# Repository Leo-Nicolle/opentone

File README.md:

# opentone

Work in progress.

This is a mp3 player in the style of an ipod classic. 

### Hardware
 - MCU: ESP32
 - Display: 2.2" LCD
 - SD Card: MicroSD
 - Audio: VS1063
 - Click wheel: MPR121

## License

- Software, firmware and docs: [MIT](LICENSE)
- Hardware (`hardware/`): [CERN-OHL-P v2](hardware/LICENSE)
- Third-party material (datasheets, vendor CAD models, footprints) keeps its own terms, see [THIRD_PARTY.md](THIRD_PARTY.md)

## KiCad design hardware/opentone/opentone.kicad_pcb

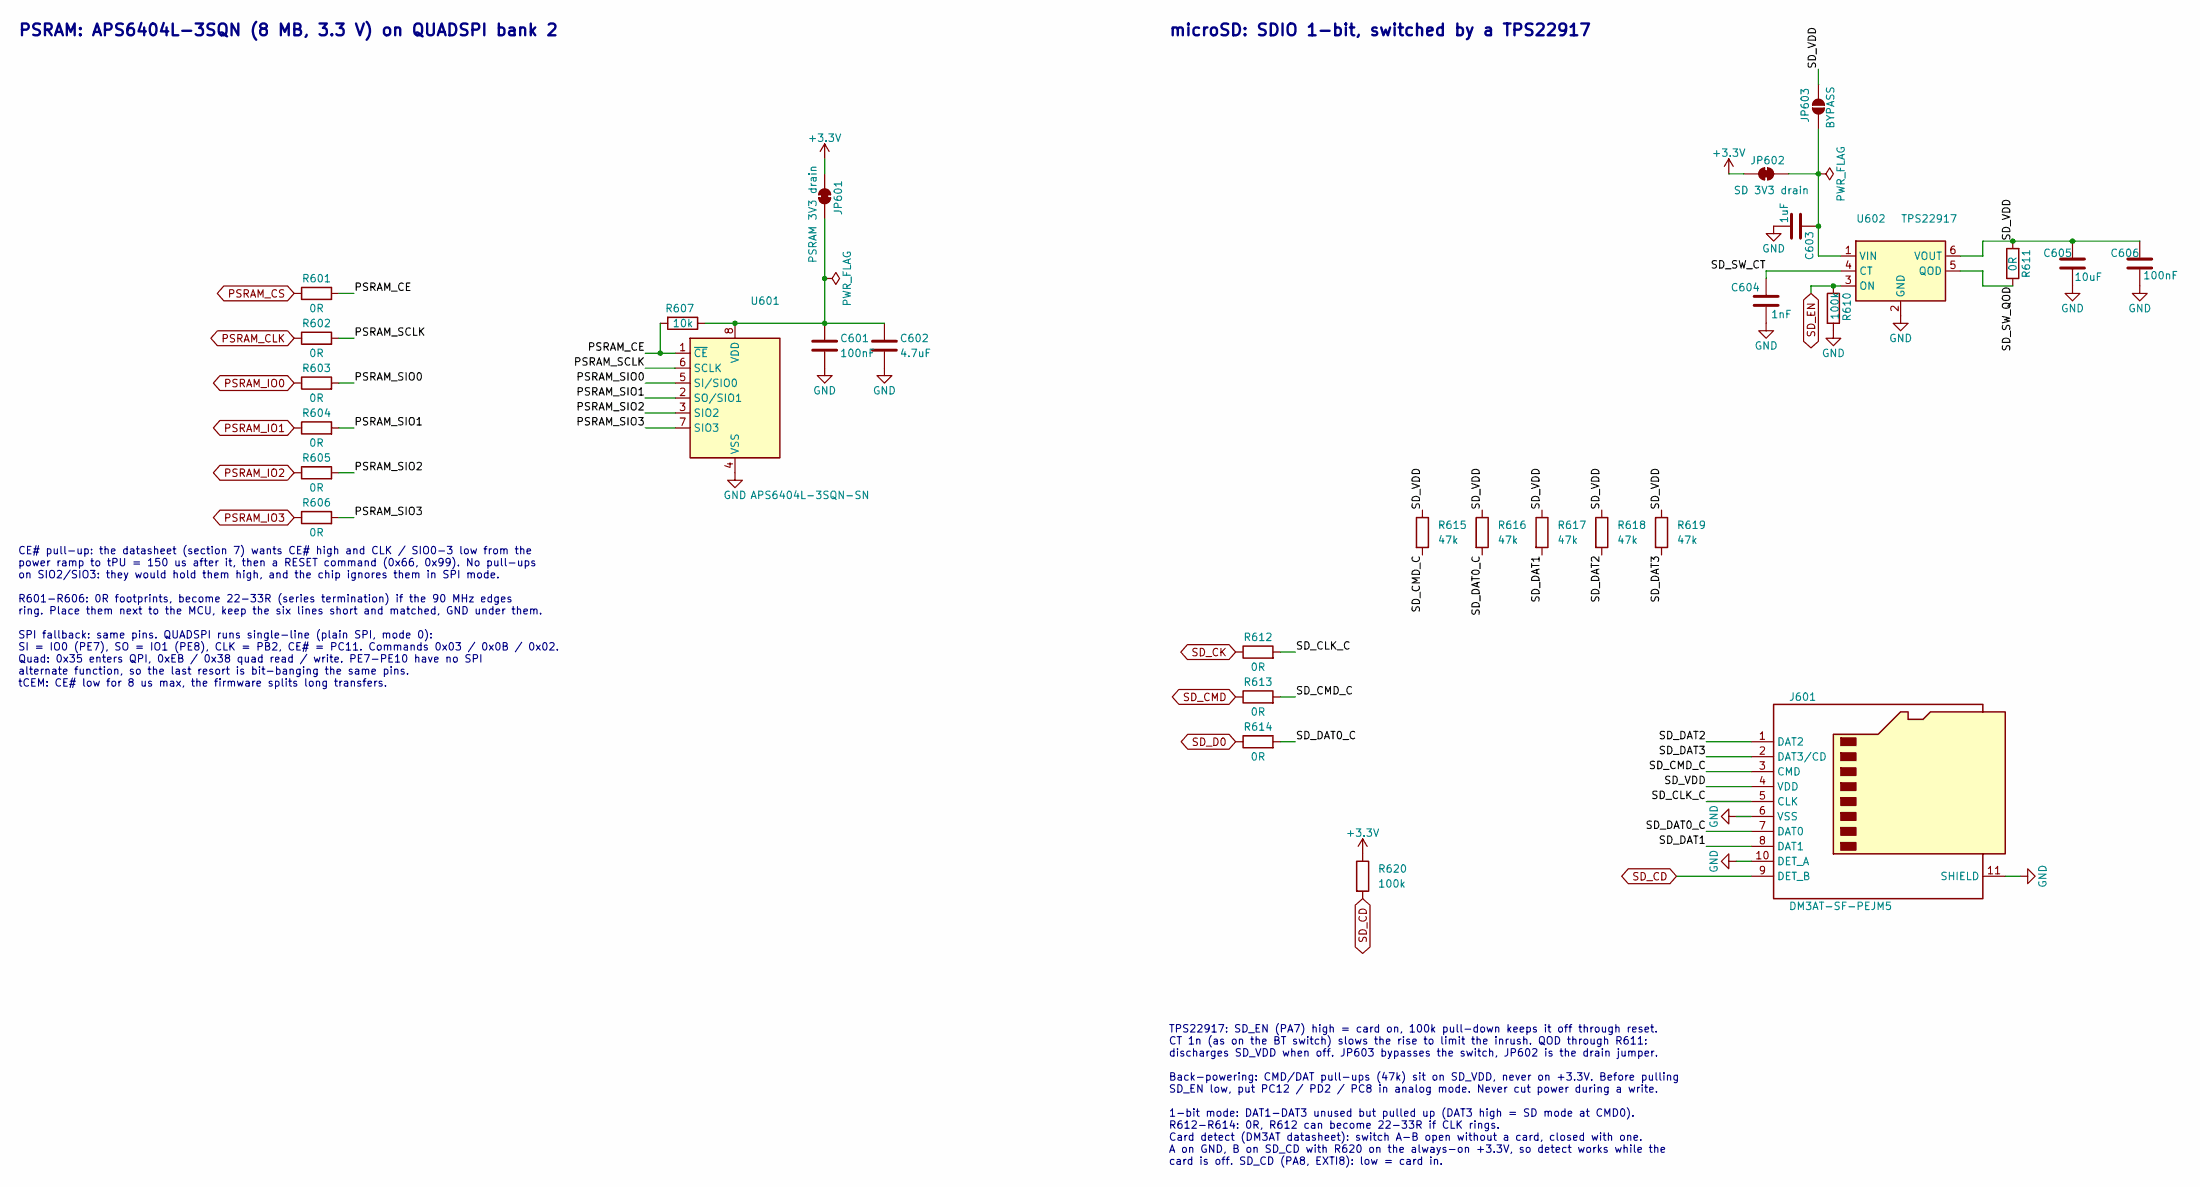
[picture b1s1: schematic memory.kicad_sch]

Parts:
C601, C606: 100nF; C_0603_1608Metric; Part number CC0603KRX7R9BB104; LCSC C14663
C602: 4.7uF; C_0603_1608Metric; Part number CL10A475KO8NNNC; LCSC C19666
C603: 1uF; C_0603_1608Metric; Part number CL10A105KB8NNNC; LCSC C15849
C604: 1nF; C_0603_1608Metric; Part number CL10B102KB8NNNC; LCSC C1588
C605: 10uF; C_0603_1608Metric; Part number CL10A106KP8NNNC; LCSC C19702
J601: DM3AT-SF-PEJM5; microSD_HC_Hirose_DM3AT-SF-PEJM5; Part number DM3AT-SF-PEJM5; LCSC C114218
JP601: PSRAM 3V3 drain; SolderJumper-2_P1.3mm_Bridged_RoundedPad1.0x1.5mm
JP602: SD 3V3 drain; SolderJumper-2_P1.3mm_Bridged_RoundedPad1.0x1.5mm
JP603: BYPASS; SolderJumper-2_P1.3mm_Open_RoundedPad1.0x1.5mm
R601, R602, R603, R604, R605, R606, R611, R612, R613, R614: 0R; R_0603_1608Metric; Part number 0603WAF0000T5E; LCSC C21189
R607: 10k; R_0603_1608Metric; Part number 0603WAF1002T5E; LCSC C25804
R610, R620: 100k; R_0603_1608Metric; Part number 0603WAF1003T5E; LCSC C25803
R615, R616, R617, R618, R619: 47k; R_0603_1608Metric; Part number 0603WAF4702T5E; LCSC C25819
U601: APS6404L-3SQN-SN; SOIC-8_3.9x4.9mm_P1.27mm; Part number APS6404L-3SQN-SN; LCSC C3028887
U602: TPS22917; SOT-23-6; Part number TPS22917DBVR; LCSC C2681320

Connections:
+3.3V: JP601.1 (A), JP602.1 (A), R620.1; also elsewhere on the board
/Memory/PSRAM_CE: R601.2, R607.2, U601.1 (~CE)
/Memory/PSRAM_SCLK: R602.2, U601.6 (SCLK)
/Memory/PSRAM_SIO0: R603.2, U601.5 (SI/SIO0)
/Memory/PSRAM_SIO1: R604.2, U601.2 (SO/SIO1)
/Memory/PSRAM_SIO2: R605.2, U601.3 (SIO2)
/Memory/PSRAM_SIO3: R606.2, U601.7 (SIO3)
/Memory/SD_CLK_C: J601.5 (CLK), R612.2
/Memory/SD_CMD_C: J601.3 (CMD), R613.2, R615.2
/Memory/SD_DAT0_C: J601.7 (DAT0), R614.2, R616.2
/Memory/SD_DAT1: J601.8 (DAT1), R617.2
/Memory/SD_DAT2: J601.1 (DAT2), R618.2
/Memory/SD_DAT3: J601.2 (DAT3/CD), R619.2
/Memory/SD_SW_CT: C604.1, U602.4 (CT)
/Memory/SD_SW_QOD: R611.1, U602.5 (QOD)
/Memory/SD_VDD: C605.1, C606.1, J601.4 (VDD), JP603.2 (B), R611.2, R615.1, R616.1, R617.1, R618.1, R619.1, U602.6 (VOUT)
GND: C601.2, C602.2, C603.2, C604.2, C605.2, C606.2, J601.6 (VSS), J601.10 (DET_A), J601.11 (SHIELD), R610.2, U601.4 (VSS), U602.2 (GND); also elsewhere on the board
unnamed: C601.1, C602.1, JP601.2 (B), R607.1, U601.8 (VDD)
unnamed: C603.1, JP602.2 (B), JP603.1 (A), U602.1 (VIN)
PSRAM_CLK: R602.1; also elsewhere on the board
PSRAM_CS: R601.1; also elsewhere on the board
PSRAM_IO0: R603.1; also elsewhere on the board
PSRAM_IO1: R604.1; also elsewhere on the board
PSRAM_IO2: R605.1; also elsewhere on the board
PSRAM_IO3: R606.1; also elsewhere on the board
SD_CD: J601.9 (DET_B), R620.2; also elsewhere on the board
SD_CK: R612.1; also elsewhere on the board
SD_CMD: R613.1; also elsewhere on the board
SD_D0: R614.1; also elsewhere on the board
SD_EN: R610.1, U602.3 (ON); also elsewhere on the board

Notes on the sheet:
microSD: SDIO 1-bit, switched by a TPS22917
TPS22917: SD_EN (PA7) high = card on, 100k pull-down keeps it off through reset. CT 1n (as on the BT switch) slows the rise to limit the inrush. QOD through R611: discharges SD_VDD when off. JP603 bypasses the switch, JP602 is the drain jumper. Back-powering: CMD/DAT pull-ups (47k) sit on SD_VDD, n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
CE# pull-up: the datasheet (section 7) wants CE# high and CLK / SIO0-3 low from the power ramp to tPU = 150 us after it, then a RESET command (0x66, 0x99). No pull-ups on SIO2/SIO3: they would hold them high, and the chip ignores them in SPI mode. R601-R606: 0R footprints, become 22-33R (series ter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
PSRAM: APS6404L-3SQN (8 MB, 3.3 V) on QUADSPI bank 2

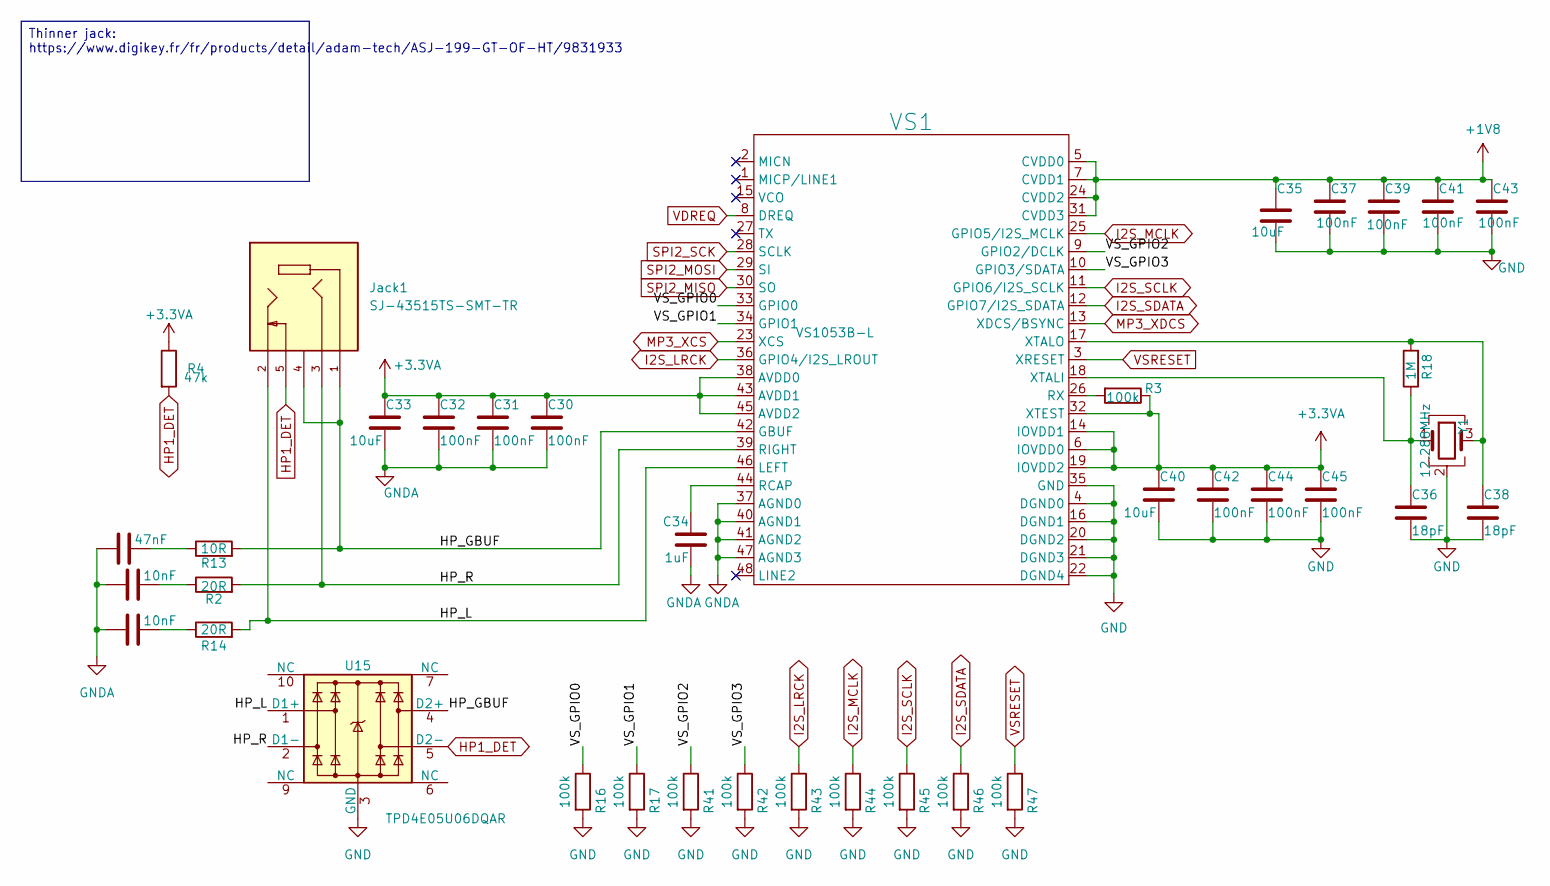
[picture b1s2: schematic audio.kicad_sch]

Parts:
C3, C29: 10nF; C_0603_1608Metric; Part number GRM1885C1H103JA01D; LCSC C85973
C9: 47nF; C_1206_3216Metric; Part number GRM31M5C1H473JA01L; LCSC C21812
C30, C31, C37, C39, C41, C42, C43, C44, C45: 100nF; C_0603_1608Metric; Part number CC0603KRX7R9BB104; LCSC C14663
C32: 100nF; C_0402_1005Metric; Part number CL05B104KO5NNNC; LCSC C1525
C33, C35, C40: 10uF; C_0603_1608Metric; Part number CL10A106KP8NNNC; LCSC C19702
C34: 1uF; C_0603_1608Metric; Part number CL10A105KB8NNNC; LCSC C15849
C36, C38: 18pF; C_0603_1608Metric; Part number CL10C180JB8NNNC; LCSC C1647
Jack1: SJ-43515TS-SMT-TR; CUI_SJ-43515TS-SMT-TR; Part number SJ-43515TS-SMT-TR; LCSC C5353507
R2, R14: 20R; R_0603_1608Metric; Part number 0603WAF200JT5E; LCSC C22950
R3, R16, R17, R41, R42, R43, R44, R45, R46, R47: 100k; R_0603_1608Metric; Part number 0603WAF1003T5E; LCSC C25803
R4: 47k; R_0603_1608Metric; Part number 0603WAF4702T5E; LCSC C25819
R13: 10R; R_0603_1608Metric; Part number 0603WAF100JT5E; LCSC C22859
R18: 1M; R_0603_1608Metric; Part number 0603WAF1004T5E; LCSC C22935
U15: TPD4E05U06DQAR; USON-10_2.5x1.0mm_P0.5mm; Part number TPD4E05U06DQAR; LCSC C138714
VS1: VS1053B-L; LQFP-48_7x7mm_P0.5mm; Part number VS1053B-L; LCSC C9922
Y1: 12.288MHz; Crystal_SMD_3225-4Pin_3.2x2.5mm; Part number TXM12.288M0004322FBCDO00T; LCSC C362472

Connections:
+1V8: C35.1, C37.1, C39.1, C41.1, C43.1, VS1.5 (CVDD0), VS1.7 (CVDD1), VS1.24 (CVDD2), VS1.31 (CVDD3); also elsewhere on the board
+3.3VA: C30.1, C31.1, C32.1, C33.1, C40.1, C42.1, C44.1, C45.1, R3.1, R4.1, VS1.6 (IOVDD0), VS1.14 (IOVDD1), VS1.19 (IOVDD2), VS1.32 (XTEST), VS1.38 (AVDD0), VS1.43 (AVDD1), VS1.45 (AVDD2); also elsewhere on the board
/Audio/HP_GBUF: Jack1.1, Jack1.4, R13.2, U15.4 (D2+), VS1.42 (GBUF)
/Audio/HP_L: Jack1.2, R14.2, U15.1 (D1+), VS1.46 (LEFT)
/Audio/HP_R: Jack1.3, R2.2, U15.2 (D1-), VS1.39 (RIGHT)
/Audio/VS_GPIO0: R16.1, VS1.33 (GPIO0)
/Audio/VS_GPIO1: R17.1, VS1.34 (GPIO1)
/Audio/VS_GPIO2: R41.1, VS1.9 (GPIO2/DCLK)
/Audio/VS_GPIO3: R42.1, VS1.10 (GPIO3/SDATA)
GND: C35.2, C36.2, C37.2, C38.2, C39.2, C40.2, C41.2, C42.2, C43.2, C44.2, C45.2, R16.2, R17.2, R41.2, R42.2, R43.2, R44.2, R45.2, R46.2, R47.2, U15.3 (GND), U15.8 (GND), VS1.4 (DGND0), VS1.16 (DGND1), VS1.20 (DGND2), VS1.21 (DGND3), VS1.22 (DGND4), VS1.35 (GND), Y1.2 (G), Y1.4 (G); also elsewhere on the board
GNDA: C3.1, C9.1, C29.1, C30.2, C31.2, C32.2, C33.2, C34.2, VS1.37 (AGND0), VS1.40 (AGND1), VS1.41 (AGND2), VS1.47 (AGND3); also elsewhere on the board
HP1_DET: Jack1.5, R4.2, U15.5 (D2-); also elsewhere on the board
I2S_LRCK: R43.1, VS1.36 (GPIO4/I2S_LROUT); also elsewhere on the board
I2S_MCLK: R44.1, VS1.25 (GPIO5/I2S_MCLK); also elsewhere on the board
I2S_SCLK: R45.1, VS1.11 (GPIO6/I2S_SCLK); also elsewhere on the board
I2S_SDATA: R46.1, VS1.12 (GPIO7/I2S_SDATA); also elsewhere on the board
MP3_XCS: VS1.23 (XCS); also elsewhere on the board
MP3_XDCS: VS1.13 (XDCS/BSYNC); also elsewhere on the board
unnamed: C3.2, R2.1
unnamed: C9.2, R13.1
unnamed: C29.2, R14.1
unnamed: C34.1, VS1.44 (RCAP)
unnamed: R3.2, VS1.26 (RX)
unnamed: C36.1, R18.1, VS1.18 (XTALI), Y1.1
unnamed: C38.1, R18.2, VS1.17 (XTALO), Y1.3
SPI2_MISO: VS1.30 (SO); also elsewhere on the board
SPI2_MOSI: VS1.29 (SI); also elsewhere on the board
SPI2_SCK: VS1.28 (SCLK); also elsewhere on the board
VDREQ: VS1.8 (DREQ); also elsewhere on the board
VSRESET: R47.1, VS1.3 (XRESET); also elsewhere on the board

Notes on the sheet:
Thinner jack: https://www.digikey.fr/fr/products/detail/adam-tech/ASJ-199-GT-OF-HT/9831933

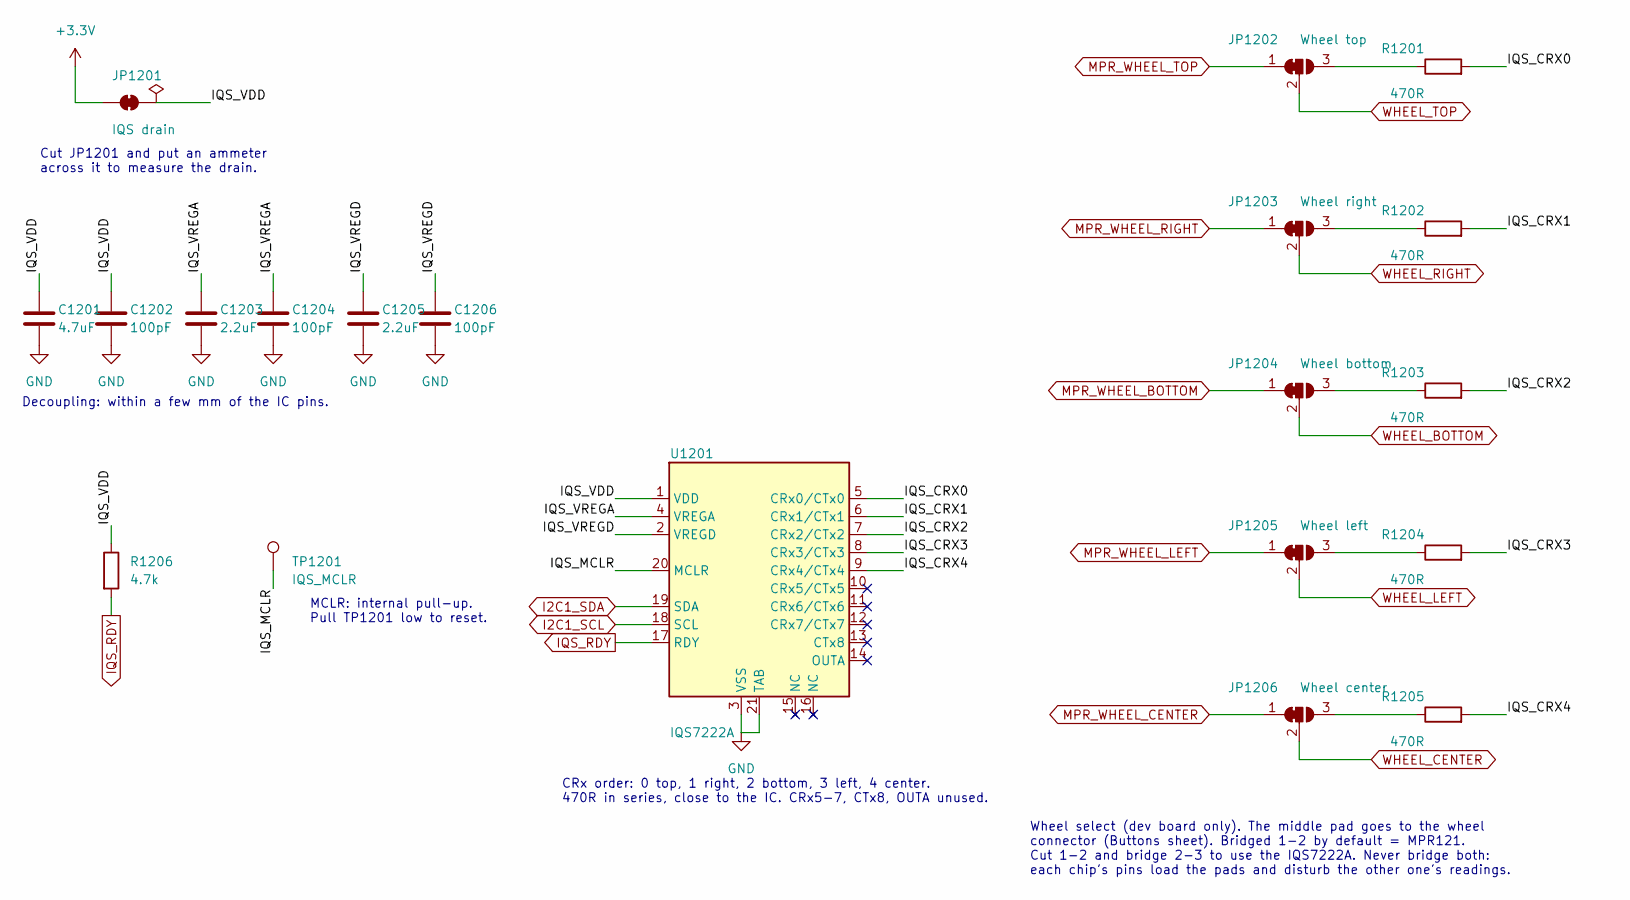
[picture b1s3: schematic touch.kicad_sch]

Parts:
C1201: 4.7uF; C_0603_1608Metric; Part number CL10A475KO8NNNC; LCSC C19666
C1202, C1204, C1206: 100pF; C_0603_1608Metric; Part number CL10C101JB8NNNC; LCSC C14858
C1203, C1205: 2.2uF; C_0603_1608Metric; Part number CL10A225KO8NNNC; LCSC C23630
JP1201: IQS drain; SolderJumper-2_P1.3mm_Bridged_RoundedPad1.0x1.5mm
JP1202: Wheel top; SolderJumper-3_P1.3mm_Bridged12_RoundedPad1.0x1.5mm
JP1203: Wheel right; SolderJumper-3_P1.3mm_Bridged12_RoundedPad1.0x1.5mm
JP1204: Wheel bottom; SolderJumper-3_P1.3mm_Bridged12_RoundedPad1.0x1.5mm
JP1205: Wheel left; SolderJumper-3_P1.3mm_Bridged12_RoundedPad1.0x1.5mm
JP1206: Wheel center; SolderJumper-3_P1.3mm_Bridged12_RoundedPad1.0x1.5mm
R1201, R1202, R1203, R1204, R1205: 470R; R_0603_1608Metric; Part number 0603WAF4700T5E; LCSC C23179
R1206: 4.7k; R_0603_1608Metric; Part number 0603WAF4701T5E; LCSC C23162
TP1201: IQS_MCLR; TestPoint_Pad_D1.0mm
U1201: IQS7222A; VQFN-20-1EP_3x3mm_P0.4mm_EP1.7x1.7mm; Part number IQS7222A001QNR; LCSC C3827627

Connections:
+3.3V: JP1201.1 (A); also elsewhere on the board
/Touch/IQS_CRX0: R1201.2, U1201.5 (CRx0/CTx0)
/Touch/IQS_CRX1: R1202.2, U1201.6 (CRx1/CTx1)
/Touch/IQS_CRX2: R1203.2, U1201.7 (CRx2/CTx2)
/Touch/IQS_CRX3: R1204.2, U1201.8 (CRx3/CTx3)
/Touch/IQS_CRX4: R1205.2, U1201.9 (CRx4/CTx4)
/Touch/IQS_MCLR: TP1201.1 (1_1), U1201.20 (MCLR)
/Touch/IQS_VDD: C1201.1, C1202.1, JP1201.2 (B), R1206.1, U1201.1 (VDD)
/Touch/IQS_VREGA: C1203.1, C1204.1, U1201.4 (VREGA)
/Touch/IQS_VREGD: C1205.1, C1206.1, U1201.2 (VREGD)
GND: C1201.2, C1202.2, C1203.2, C1204.2, C1205.2, C1206.2, U1201.3 (VSS), U1201.21 (TAB); also elsewhere on the board
I2C1_SCL: U1201.18 (SCL); also elsewhere on the board
I2C1_SDA: U1201.19 (SDA); also elsewhere on the board
IQS_RDY: R1206.2, U1201.17 (RDY); also elsewhere on the board
MPR_WHEEL_BOTTOM: JP1204.1 (A); also elsewhere on the board
MPR_WHEEL_CENTER: JP1206.1 (A); also elsewhere on the board
MPR_WHEEL_LEFT: JP1205.1 (A); also elsewhere on the board
MPR_WHEEL_RIGHT: JP1203.1 (A); also elsewhere on the board
MPR_WHEEL_TOP: JP1202.1 (A); also elsewhere on the board
unnamed: JP1202.3 (B), R1201.1
unnamed: JP1203.3 (B), R1202.1
unnamed: JP1204.3 (B), R1203.1
unnamed: JP1205.3 (B), R1204.1
unnamed: JP1206.3 (B), R1205.1
WHEEL_BOTTOM: JP1204.2 (C); also elsewhere on the board
WHEEL_CENTER: JP1206.2 (C); also elsewhere on the board
WHEEL_LEFT: JP1205.2 (C); also elsewhere on the board
WHEEL_RIGHT: JP1203.2 (C); also elsewhere on the board
WHEEL_TOP: JP1202.2 (C); also elsewhere on the board

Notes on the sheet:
MCLR: internal pull-up. Pull TP1201 low to reset.
Decoupling: within a few mm of the IC pins.
CRx order: 0 top, 1 right, 2 bottom, 3 left, 4 center. 470R in series, close to the IC. CRx5-7, CTx8, OUTA unused.
Cut JP1201 and put an ammeter across it to measure the drain.
Wheel select (dev board only). The middle pad goes to the wheel connector (Buttons sheet). Bridged 1-2 by default = MPR121. Cut 1-2 and bridge 2-3 to use the IQS7222A. Never bridge both: each chip's pins load the pads and disturb the other one's readings.

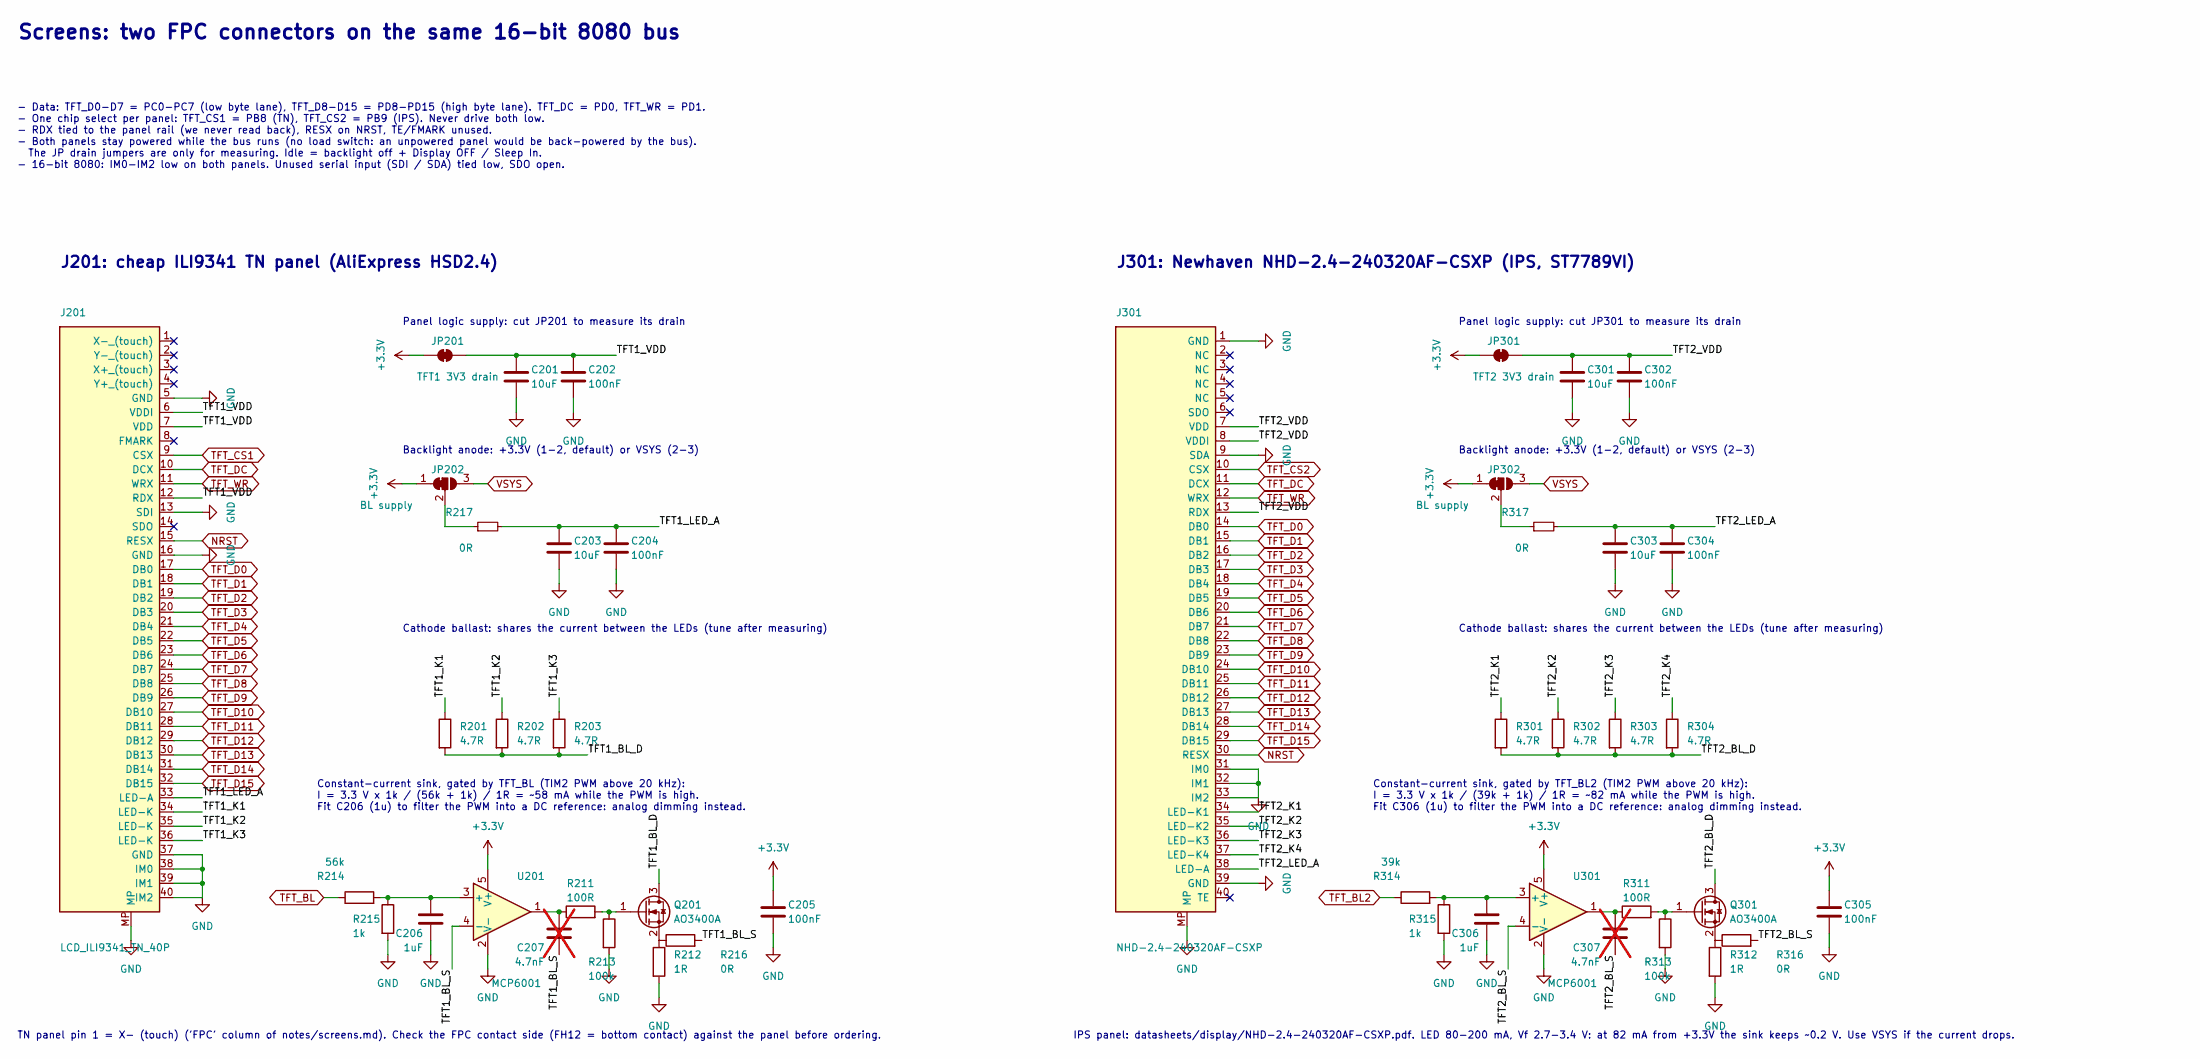
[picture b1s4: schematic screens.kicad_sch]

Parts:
C201, C301: 10uF; C_0603_1608Metric; Part number CL10A106KP8NNNC; LCSC C19702
C202, C204, C205, C302, C304, C305: 100nF; C_0603_1608Metric; Part number CC0603KRX7R9BB104; LCSC C14663
C203, C303: 10uF; C_0603_1608Metric; Part number CL10A106MA8NRNC; LCSC C96446
C206, C306: 1uF; C_0603_1608Metric; Part number CL10A105KB8NNNC; LCSC C15849
C207, C307: 4.7nF; C_0603_1608Metric; Part number 0603B472K500NT; LCSC C53987; not fitted
J201: LCD_ILI9341_TN_40P; Hirose_FH12-40S-0.5SH_1x40-1MP_P0.50mm_Horizontal; Part number FH12-40S-0.5SH(55); LCSC C202114
J301: NHD-2.4-240320AF-CSXP; Hirose_FH12-40S-0.5SH_1x40-1MP_P0.50mm_Horizontal; Part number FH12-40S-0.5SH(55); LCSC C202114
JP201: TFT1 3V3 drain; SolderJumper-2_P1.3mm_Bridged_RoundedPad1.0x1.5mm
JP202, JP302: BL supply; SolderJumper-3_P1.3mm_Bridged12_RoundedPad1.0x1.5mm
JP301: TFT2 3V3 drain; SolderJumper-2_P1.3mm_Bridged_RoundedPad1.0x1.5mm
Q201, Q301: AO3400A; SOT-23; Part number AO3400A; LCSC C20917
R201, R202, R203, R301, R302, R303, R304: 4.7R; R_0603_1608Metric; Part number 0603WAF470KT5E; LCSC C23164
R211, R311: 100R; R_0603_1608Metric; Part number 0603WAF1000T5E; LCSC C22775
R212, R312: 1R; R_0603_1608Metric; Part number 0603WAF100KT5E; LCSC C22936
R213, R313: 100k; R_0603_1608Metric; Part number 0603WAF1003T5E; LCSC C25803
R214: 56k; R_0603_1608Metric; Part number 0603WAF5602T5E; LCSC C23206
R215, R315: 1k; R_0603_1608Metric; Part number 0603WAF1001T5E; LCSC C21190
R216, R217, R316, R317: 0R; R_0603_1608Metric; Part number 0603WAF0000T5E; LCSC C21189
R314: 39k; R_0603_1608Metric; Part number 0603WAF3902T5E; LCSC C23153
U201, U301: MCP6001; SOT-23-5; Part number MCP6001T-I/OT; LCSC C116490

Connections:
+3.3V: C205.1, C305.1, JP201.1 (A), JP202.1 (A), JP301.1 (A), JP302.1 (A), U201.5 (V+), U301.5 (V+); also elsewhere on the board
/Screens/TFT1_BL_D: Q201.3 (D), R201.2, R202.2, R203.2
/Screens/TFT1_BL_S: C207.2, R216.2, U201.4 (-)
/Screens/TFT1_K1: J201.34 (LED-K), R201.1
/Screens/TFT1_K2: J201.35 (LED-K), R202.1
/Screens/TFT1_K3: J201.36 (LED-K), R203.1
/Screens/TFT1_LED_A: C203.1, C204.1, J201.33 (LED-A), R217.2
/Screens/TFT1_VDD: C201.1, C202.1, J201.6 (VDDI), J201.7 (VDD), J201.12 (RDX), JP201.2 (B)
/Screens/TFT2_BL_D: Q301.3 (D), R301.2, R302.2, R303.2, R304.2
/Screens/TFT2_BL_S: C307.2, R316.2, U301.4 (-)
/Screens/TFT2_K1: J301.34 (LED-K1), R301.1
/Screens/TFT2_K2: J301.35 (LED-K2), R302.1
/Screens/TFT2_K3: J301.36 (LED-K3), R303.1
/Screens/TFT2_K4: J301.37 (LED-K4), R304.1
/Screens/TFT2_LED_A: C303.1, C304.1, J301.38 (LED-A), R317.2
/Screens/TFT2_VDD: C301.1, C302.1, J301.7 (VDD), J301.8 (VDDI), J301.13 (RDX), JP301.2 (B)
GND: C201.2, C202.2, C203.2, C204.2, C205.2, C206.2, C301.2, C302.2, C303.2, C304.2, C305.2, C306.2, J201.5 (GND), J201.13 (SDI), J201.16 (GND), J201.37 (GND), J201.38 (IM0), J201.39 (IM1), J201.40 (IM2), J201.MP, J301.1 (GND), J301.9 (SDA), J301.31 (IM0), J301.32 (IM1), J301.33 (IM2), J301.39 (GND), J301.MP, R212.2, R213.2, R215.2, R312.2, R313.2, R315.2, U201.2 (V-), U301.2 (V-); also elsewhere on the board
NRST: J201.15 (RESX), J301.30 (RESX); also elsewhere on the board
unnamed: C207.1, R211.1, U201.1
unnamed: C307.1, R311.1, U301.1
unnamed: JP202.2 (C), R217.1
unnamed: JP302.2 (C), R317.1
unnamed: Q201.1 (G), R211.2, R213.1
unnamed: Q201.2 (S), R212.1, R216.1
unnamed: Q301.1 (G), R311.2, R313.1
unnamed: Q301.2 (S), R312.1, R316.1
unnamed: C206.1, R214.2, R215.1, U201.3 (+)
unnamed: C306.1, R314.2, R315.1, U301.3 (+)
TFT_BL: R214.1; also elsewhere on the board
TFT_BL2: R314.1; also elsewhere on the board
TFT_CS1: J201.9 (CSX); also elsewhere on the board
TFT_CS2: J301.10 (CSX); also elsewhere on the board
TFT_D0: J201.17 (DB0), J301.14 (DB0); also elsewhere on the board
TFT_D1: J201.18 (DB1), J301.15 (DB1); also elsewhere on the board
TFT_D2: J201.19 (DB2), J301.16 (DB2); also elsewhere on the board
TFT_D3: J201.20 (DB3), J301.17 (DB3); also elsewhere on the board
TFT_D4: J201.21 (DB4), J301.18 (DB4); also elsewhere on the board
TFT_D5: J201.22 (DB5), J301.19 (DB5); also elsewhere on the board
TFT_D6: J201.23 (DB6), J301.20 (DB6); also elsewhere on the board
TFT_D7: J201.24 (DB7), J301.21 (DB7); also elsewhere on the board
TFT_D8: J201.25 (DB8), J301.22 (DB8); also elsewhere on the board
TFT_D9: J201.26 (DB9), J301.23 (DB9); also elsewhere on the board
TFT_D10: J201.27 (DB10), J301.24 (DB10); also elsewhere on the board
TFT_D11: J201.28 (DB11), J301.25 (DB11); also elsewhere on the board
TFT_D12: J201.29 (DB12), J301.26 (DB12); also elsewhere on the board
TFT_D13: J201.30 (DB13), J301.27 (DB13); also elsewhere on the board
TFT_D14: J201.31 (DB14), J301.28 (DB14); also elsewhere on the board
TFT_D15: J201.32 (DB15), J301.29 (DB15); also elsewhere on the board
TFT_DC: J201.10 (DCX), J301.11 (DCX); also elsewhere on the board
TFT_WR: J201.11 (WRX), J301.12 (WRX); also elsewhere on the board
VSYS: JP202.3 (B), JP302.3 (B); also elsewhere on the board

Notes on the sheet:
Panel logic supply: cut JP201 to measure its drain
TN panel pin 1 = X- (touch) ('FPC' column of notes/screens.md). Check the FPC contact side (FH12 = bottom contact) against the panel before ordering.
Backlight anode: +3.3V (1-2, default) or VSYS (2-3)
- Data: TFT_D0-D7 = PC0-PC7 (low byte lane), TFT_D8-D15 = PD8-PD15 (high byte lane). TFT_DC = PD0, TFT_WR = PD1. - One chip select per panel: TFT_CS1 = PB8 (TN), TFT_CS2 = PB9 (IPS). Never drive both low. - RDX tied to the panel rail (we never read back), RESX on NRST, TE/FMARK unused. - Both panel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
Constant-current sink, gated by TFT_BL (TIM2 PWM above 20 kHz): I = 3.3 V x 1k / (56k + 1k) / 1R = ~58 mA while the PWM is high. Fit C206 (1u) to filter the PWM into a DC reference: analog dimming instead.
Screens: two FPC connectors on the same 16-bit 8080 bus
IPS panel: datasheets/display/NHD-2.4-240320AF-CSXP.pdf. LED 80-200 mA, Vf 2.7-3.4 V: at 82 mA from +3.3V the sink keeps ~0.2 V. Use VSYS if the current drops.
Panel logic supply: cut JP301 to measure its drain
J201: cheap ILI9341 TN panel (AliExpress HSD2.4)
Constant-current sink, gated by TFT_BL2 (TIM2 PWM above 20 kHz): I = 3.3 V x 1k / (39k + 1k) / 1R = ~82 mA while the PWM is high. Fit C306 (1u) to filter the PWM into a DC reference: analog dimming instead.
J301: Newhaven NHD-2.4-240320AF-CSXP (IPS, ST7789VI)
Cathode ballast: shares the current between the LEDs (tune after measuring)

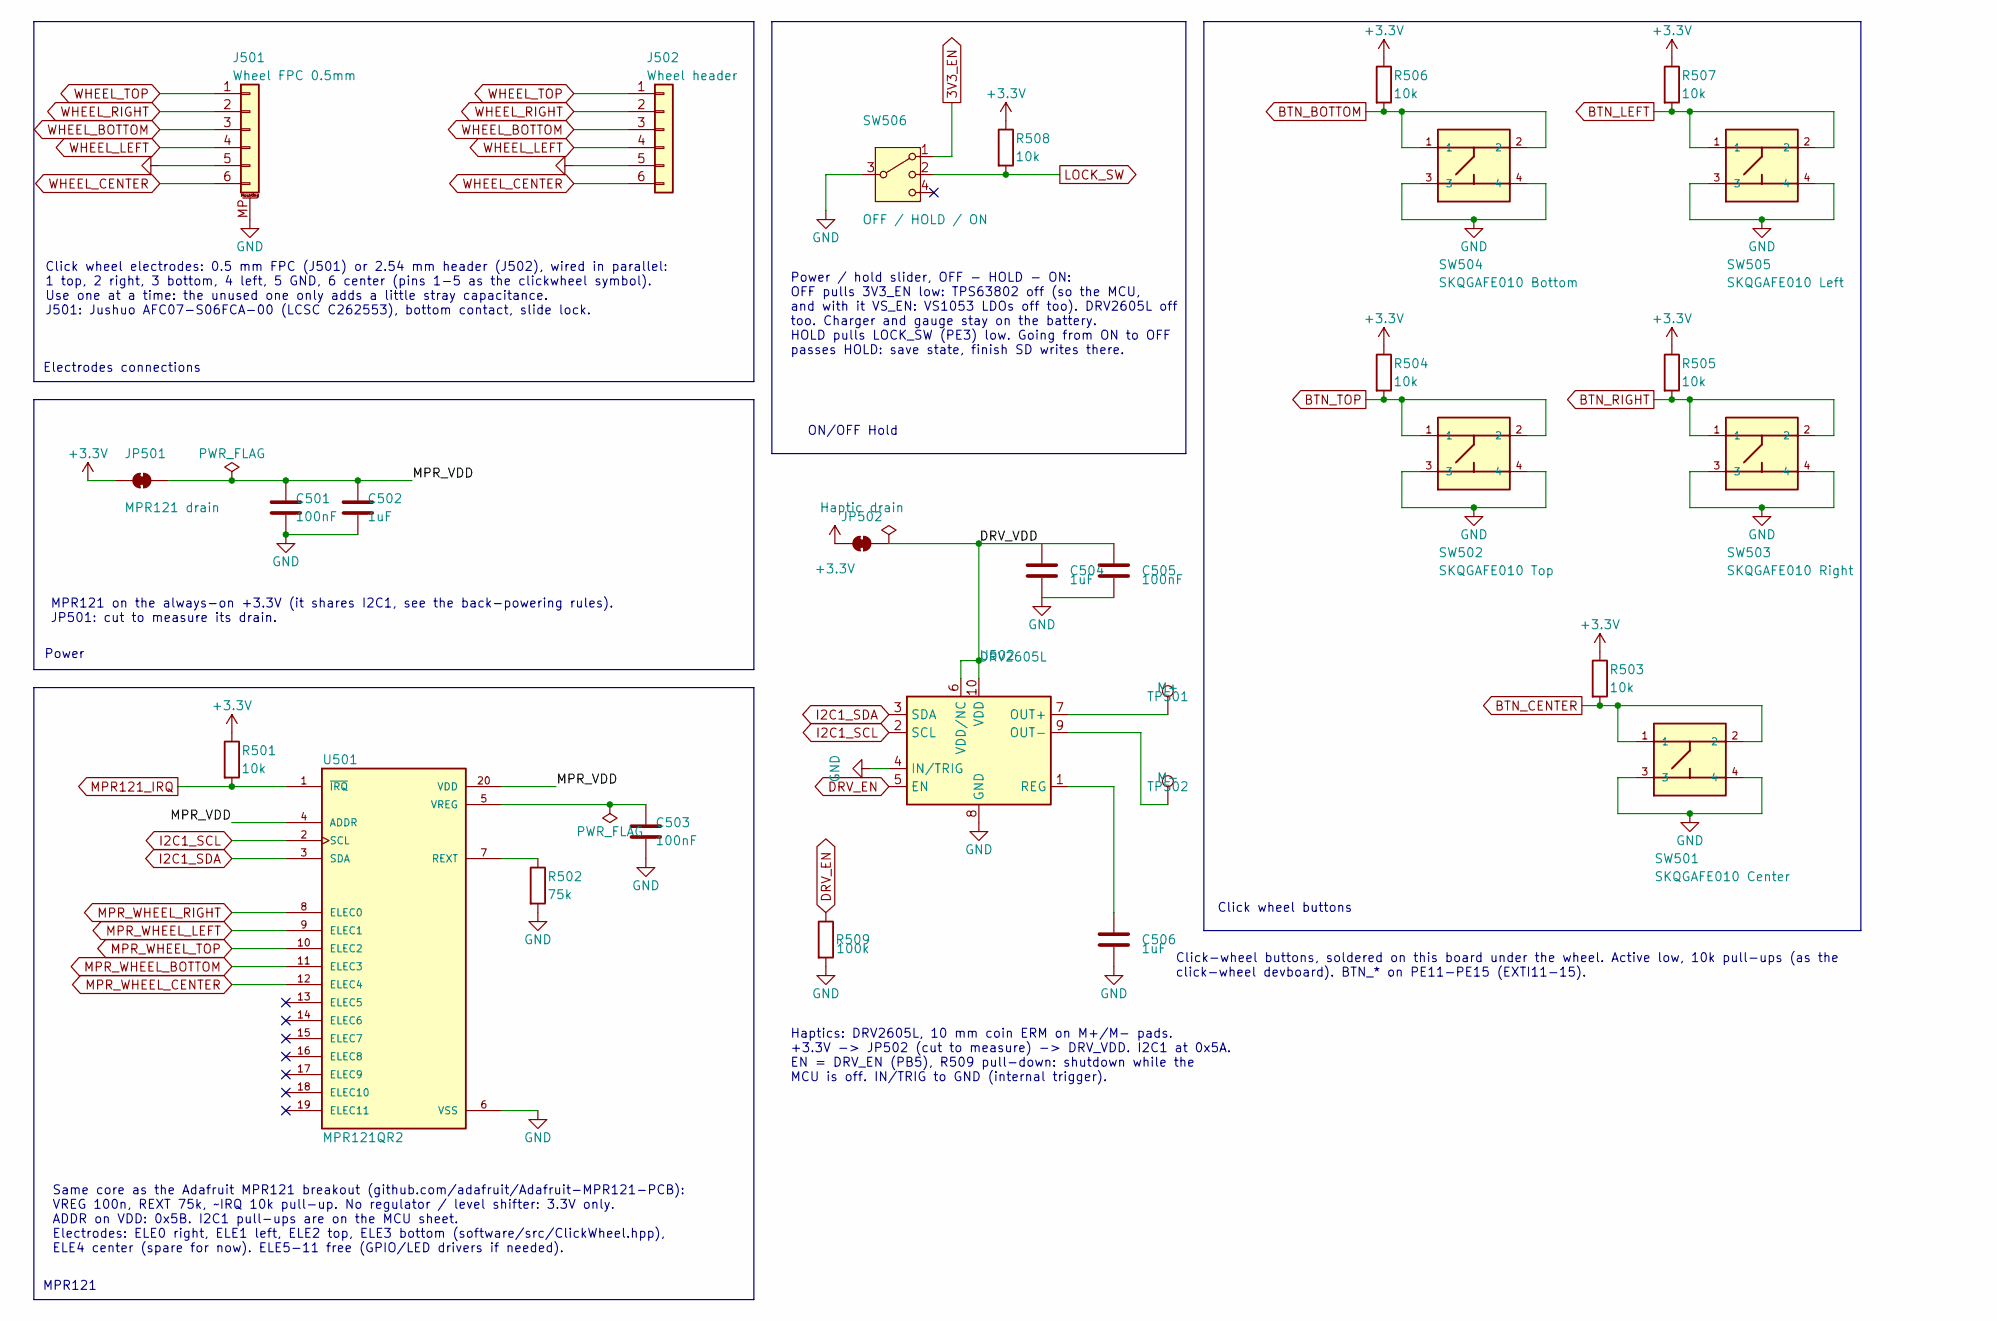
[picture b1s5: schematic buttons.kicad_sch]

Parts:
C501, C503, C505: 100nF; C_0603_1608Metric; Part number CC0603KRX7R9BB104; LCSC C14663
C502, C504, C506: 1uF; C_0603_1608Metric; Part number CL10A105KB8NNNC; LCSC C15849
J501: Wheel FPC 0.5mm; Jushuo_AFC07-S06FCA-00_1x6-1MP_P0.50_Horizontal; Part number AFC07-S06FCA-00; LCSC C262553
J502: Wheel header; PinHeader_1x06_P2.54mm_Vertical
JP501: MPR121 drain; SolderJumper-2_P1.3mm_Bridged_RoundedPad1.0x1.5mm
JP502: Haptic drain; SolderJumper-2_P1.3mm_Bridged_RoundedPad1.0x1.5mm
R501, R503, R504, R505, R506, R507, R508: 10k; R_0603_1608Metric; Part number 0603WAF1002T5E; LCSC C25804
R502: 75k; R_0603_1608Metric; Part number 0603WAF7502T5E; LCSC C23242
R509: 100k; R_0603_1608Metric; Part number 0603WAF1003T5E; LCSC C25803
SW501: SKQGAFE010 Center; SW_SKQGAFE010; Part number SKQGAFE010; LCSC C202424
SW502: SKQGAFE010 Top; SW_SKQGAFE010; Part number SKQGAFE010; LCSC C202424
SW503: SKQGAFE010 Right; SW_SKQGAFE010; Part number SKQGAFE010; LCSC C202424
SW504: SKQGAFE010 Bottom; SW_SKQGAFE010; Part number SKQGAFE010; LCSC C202424
SW505: SKQGAFE010 Left; SW_SKQGAFE010; Part number SKQGAFE010; LCSC C202424
SW506: OFF / HOLD / ON; SW_SP3T_PCM13; Part number PCM13SMTR; LCSC C221842
TP501: M+; TestPoint_Pad_1.5x1.5mm
TP502: M-; TestPoint_Pad_1.5x1.5mm
U501: MPR121QR2; mpr121qr2; Part number MPR121QR2; LCSC C91322
U502: DRV2605L; VSSOP-10_3x3mm_P0.5mm; Part number DRV2605LDGSR; LCSC C527464

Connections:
3V3_EN: SW506.1; also elsewhere on the board
+3.3V: JP501.1 (A), JP502.1 (A), R501.1, R503.1, R504.1, R505.1, R506.1, R507.1, R508.1; also elsewhere on the board
/Buttons/DRV_VDD: C504.1, C505.1, JP502.2 (B), U502.6 (VDD/NC), U502.10 (VDD)
/Buttons/MPR_VDD: C501.1, C502.1, JP501.2 (B), U501.4 (ADDR), U501.20 (VDD)
BTN_BOTTOM: R506.2, SW504.1, SW504.2; also elsewhere on the board
BTN_CENTER: R503.2, SW501.1, SW501.2; also elsewhere on the board
BTN_LEFT: R507.2, SW505.1, SW505.2; also elsewhere on the board
BTN_RIGHT: R505.2, SW503.1, SW503.2; also elsewhere on the board
BTN_TOP: R504.2, SW502.1, SW502.2; also elsewhere on the board
DRV_EN: R509.1, U502.5 (EN); also elsewhere on the board
GND: C501.2, C502.2, C503.2, C504.2, C505.2, C506.2, J501.5, J501.MP (MountPin), J502.5, R502.2, R509.2, SW501.3, SW501.4, SW502.3, SW502.4, SW503.3, SW503.4, SW504.3, SW504.4, SW505.3, SW505.4, SW506.3, U501.6 (VSS), U502.4 (IN/TRIG), U502.8 (GND); also elsewhere on the board
I2C1_SCL: U501.2 (SCL), U502.2 (SCL); also elsewhere on the board
I2C1_SDA: U501.3 (SDA), U502.3 (SDA); also elsewhere on the board
LOCK_SW: R508.2, SW506.2; also elsewhere on the board
MPR121_IRQ: R501.2, U501.1 (~IRQ); also elsewhere on the board
MPR_WHEEL_BOTTOM: U501.11 (ELEC3); also elsewhere on the board
MPR_WHEEL_CENTER: U501.12 (ELEC4); also elsewhere on the board
MPR_WHEEL_LEFT: U501.9 (ELEC1); also elsewhere on the board
MPR_WHEEL_RIGHT: U501.8 (ELEC0); also elsewhere on the board
MPR_WHEEL_TOP: U501.10 (ELEC2); also elsewhere on the board
unnamed: R502.1, U501.7 (REXT)
unnamed: C503.1, U501.5 (VREG)
unnamed: TP501.1 (1_1), U502.7 (OUT+)
unnamed: TP502.1 (1_1), U502.9 (OUT-)
unnamed: C506.1, U502.1 (REG)
WHEEL_BOTTOM: J501.3, J502.3; also elsewhere on the board
WHEEL_CENTER: J501.6, J502.6; also elsewhere on the board
WHEEL_LEFT: J501.4, J502.4; also elsewhere on the board
WHEEL_RIGHT: J501.2, J502.2; also elsewhere on the board
WHEEL_TOP: J501.1, J502.1; also elsewhere on the board

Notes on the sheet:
Power / hold slider, OFF - HOLD - ON: OFF pulls 3V3_EN low: TPS63802 off (so the MCU, and with it VS_EN: VS1053 LDOs off too). DRV2605L off too. Charger and gauge stay on the battery. HOLD pulls LOCK_SW (PE3) low. Going from ON to OFF passes HOLD: save state, finish SD writes there.
Haptics: DRV2605L, 10 mm coin ERM on M+/M- pads. +3.3V -> JP502 (cut to measure) -> DRV_VDD. I2C1 at 0x5A. EN = DRV_EN (PB5), R509 pull-down: shutdown while the MCU is off. IN/TRIG to GND (internal trigger).
MPR121
Click wheel buttons
Electrodes connections
Same core as the Adafruit MPR121 breakout (github.com/adafruit/Adafruit-MPR121-PCB): VREG 100n, REXT 75k, ~IRQ 10k pull-up. No regulator / level shifter: 3.3V only. ADDR on VDD: 0x5B. I2C1 pull-ups are on the MCU sheet. Electrodes: ELE0 right, ELE1 left, ELE2 top, ELE3 bottom (software/src/ClickWhe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
Click wheel electrodes: 0.5 mm FPC (J501) or 2.54 mm header (J502), wired in parallel: 1 top, 2 right, 3 bottom, 4 left, 5 GND, 6 center (pins 1-5 as the clickwheel symbol). Use one at a time: the unused one only adds a little stray capacitance. J501: Jushuo AFC07-S06FCA-00 (LCSC C262553), bottom c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
MPR121 on the always-on +3.3V (it shares I2C1, see the back-powering rules). JP501: cut to measure its drain.
ON/OFF Hold
Click-wheel buttons, soldered on this board under the wheel. Active low, 10k pull-ups (as the click-wheel devboard). BTN_* on PE11-PE15 (EXTI11-15).
Power
